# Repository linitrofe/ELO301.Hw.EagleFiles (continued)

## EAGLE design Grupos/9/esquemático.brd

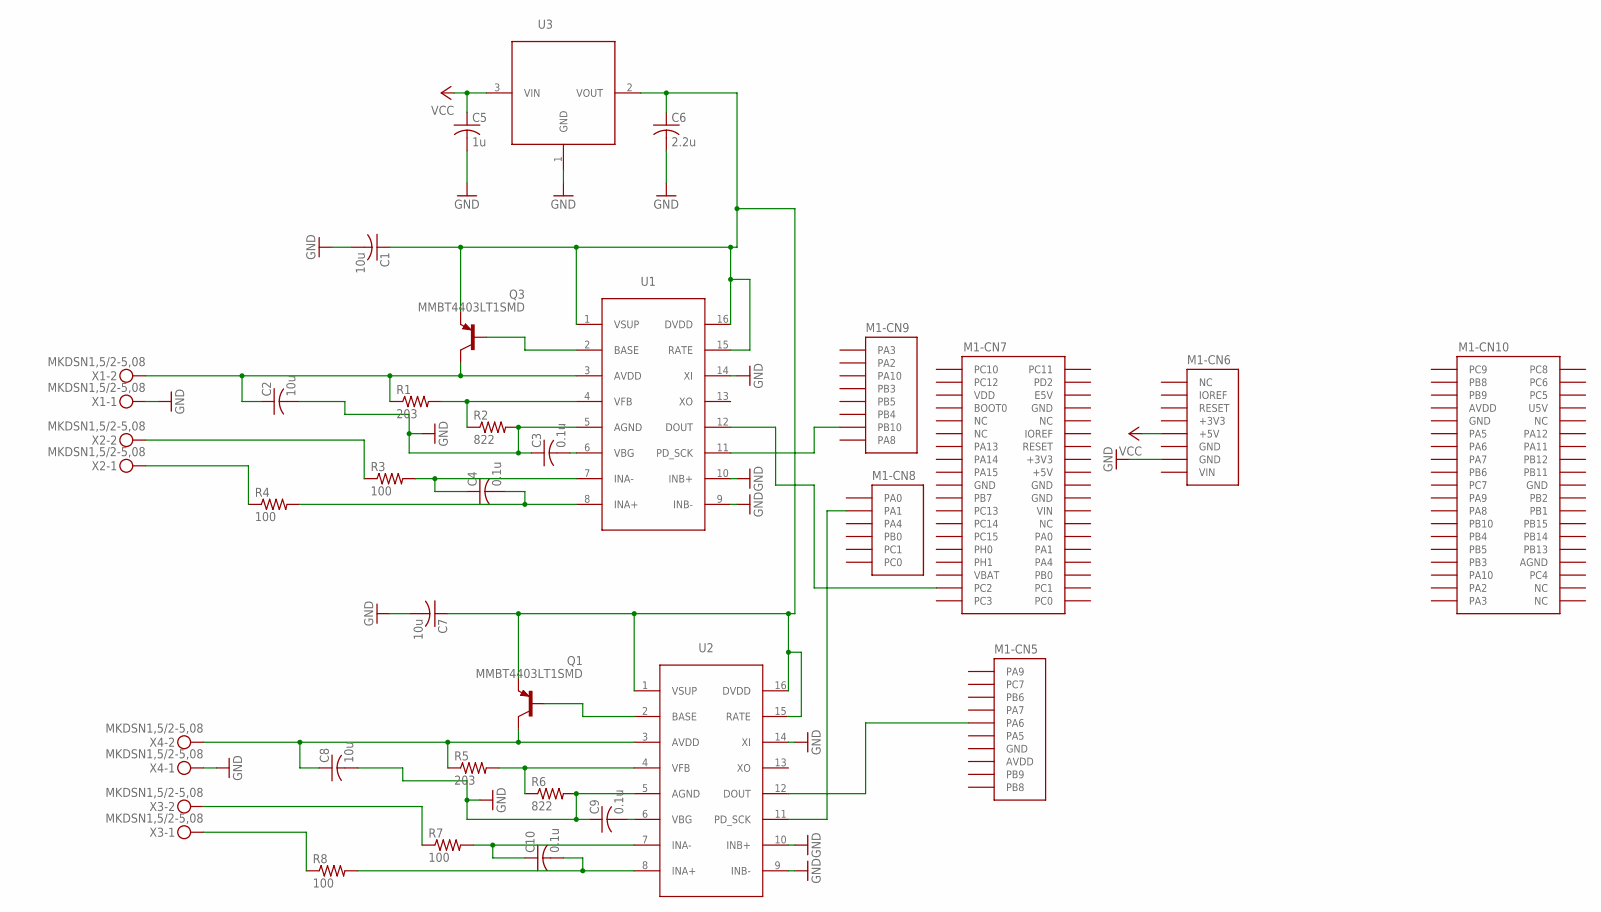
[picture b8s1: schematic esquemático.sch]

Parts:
C1, C2, C7, C8: 10u; C0805
C3, C4, C9, C10: 0.1u; C0805
C5: 1u; C0805
C6: 2.2u; C0805
M1: NUCLEO-L452RE; NUCLEO-64
Q1, Q3: MMBT4403LT1SMD; SOT23-BEC; PARTNO BCR573E6327
R1, R5: 203; R0805
R2, R6: 822; R0805
R3, R4, R7, R8: 100; R0805
U1, U2: HX711SOIC127P600X140-16N; SOIC127P600X140-16N; PARTNO HX711
U3: AP2210N-4.0TRG1; SOT-23-3; PARTNO AP2210N-4.0TRG1
X1, X2, X3, X4: MKDSN1,5/2-5,08; PARTNO MKDSN1,5/2-5,08

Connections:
+3V3: M1.CN6-4 (+3V3), M1.CN7-16 (+3V3)
+5V: M1.CN7-18 (+5V)
AGND: M1.CN10-32 (AGND)
AVDD: M1.CN5-8 (AVDD), M1.CN10-7 (AVDD)
GND: C1.2, C2.2, C3.1, C5.2, C6.2, C7.2, C8.2, C9.1, M1.CN5-7 (GND), M1.CN6-6 (GND), M1.CN6-7 (GND), M1.CN7-8 (GND), M1.CN7-19 (GND), M1.CN7-20 (GND), M1.CN7-22 (GND), M1.CN10-9 (GND), M1.CN10-20 (GND), R2.2, R6.2, U1.5 (AGND), U1.9 (INB-), U1.10 (INB+), U1.14 (XI), U2.5 (AGND), U2.9 (INB-), U2.10 (INB+), U2.14 (XI), U3.1 (GND), X1.1, X4.1
IOREF: M1.CN6-2 (IOREF)
unnamed: C2.1, Q3.C, R1.1, U1.3 (AVDD), X1.2
unnamed: C4.1, R3.2, U1.7 (INA-)
unnamed: M1.CN9-7 (PB10), U1.11 (PD_SCK)
unnamed: R1.2, R2.1, U1.4 (VFB)
unnamed: R3.1, X2.2
unnamed: C4.2, R4.2, U1.8 (INA+)
unnamed: R4.1, X2.1
unnamed: C3.2, U1.6 (VBG)
unnamed: C8.1, Q1.C, R5.1, U2.3 (AVDD), X4.2
unnamed: Q3.B, U1.2 (BASE)
unnamed: R5.2, R6.1, U2.4 (VFB)
unnamed: C10.1, R7.2, U2.7 (INA-)
unnamed: R7.1, X3.2
unnamed: C10.2, R8.2, U2.8 (INA+)
unnamed: R8.1, X3.1
unnamed: C9.2, U2.6 (VBG)
unnamed: M1.CN5-5 (PA6), U2.12 (DOUT)
unnamed: Q1.B, U2.2 (BASE)
unnamed: M1.CN7-35 (PC2), U1.12 (DOUT)
unnamed: M1.CN8-2 (PA1), U2.11 (PD_SCK)
unnamed: C1.1, C6.1, C7.1, Q1.E, Q3.E, U1.1 (VSUP), U1.15 (RATE), U1.16 (DVDD), U2.1 (VSUP), U2.15 (RATE), U2.16 (DVDD), U3.2 (VOUT)
U5V: M1.CN10-8 (U5V)
VBAT: M1.CN7-33 (VBAT)
VCC: C5.1, M1.CN6-5 (+5V), U3.3 (VIN)
VDD: M1.CN7-5 (VDD)
VIN: M1.CN6-8 (VIN), M1.CN7-24 (VIN)

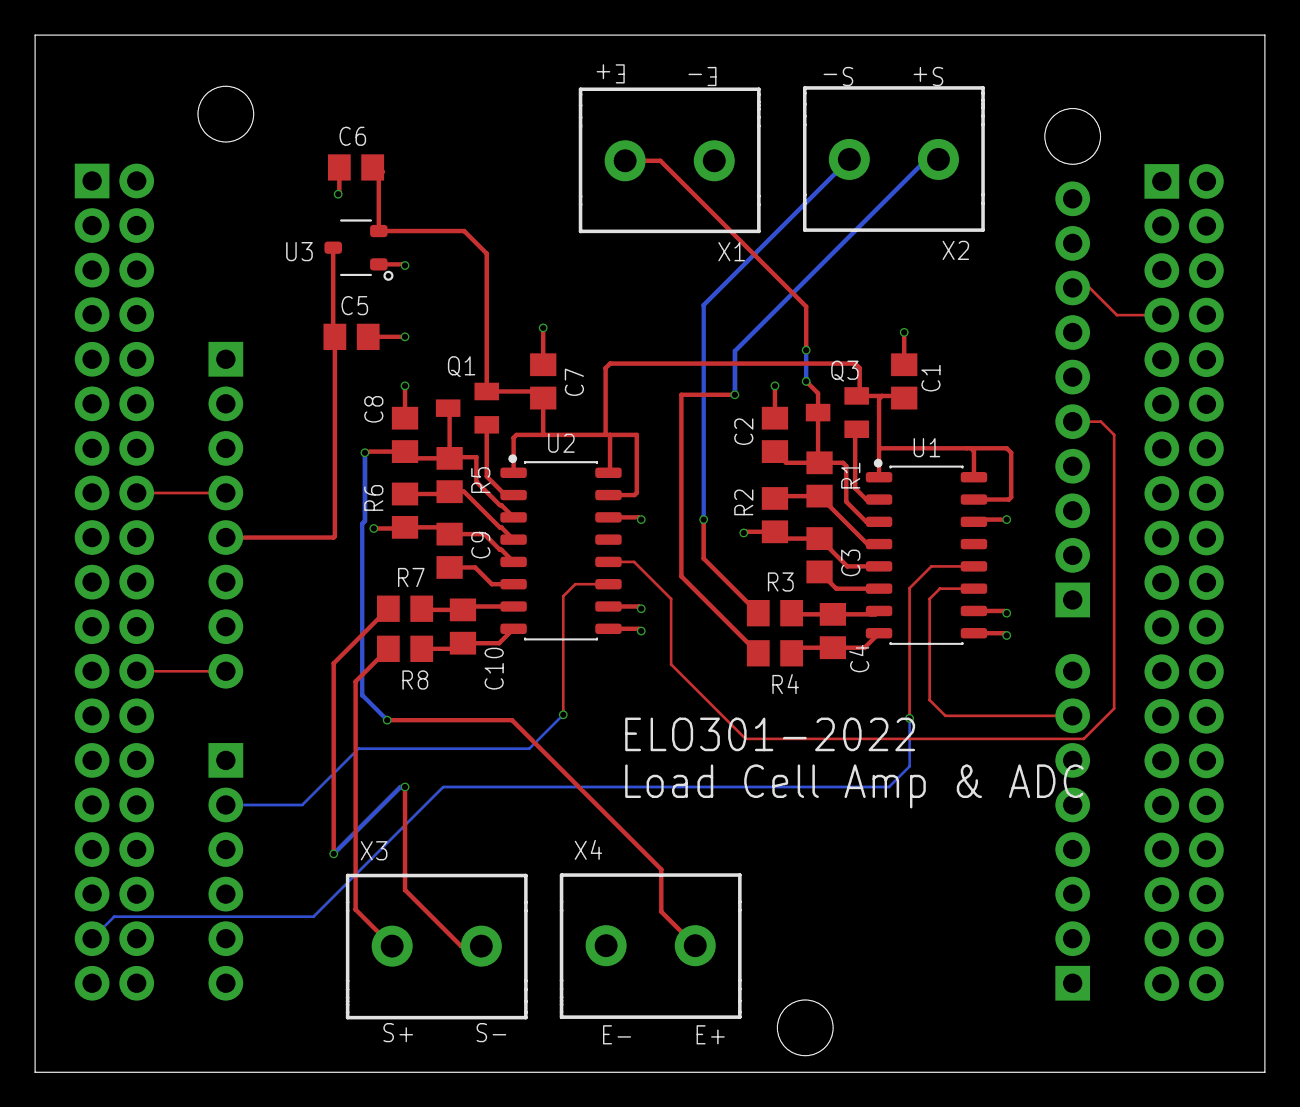
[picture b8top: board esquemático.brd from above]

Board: 2 copper layers, 70.1 x 59.1 mm, 28 parts (0 on the bottom side), 26 nets.

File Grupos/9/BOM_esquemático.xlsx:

Qty | Value | Device | Package | Parts | Description | PARTNO | POPULARITY | SPICEPREFIX | Column1
2 |  | HX711SOIC127P600X140-16N | SOIC127P600X140-16N | U1, U2 |  | HX711
1 |  | NUCLEO-L452RE | NUCLEO-64 | M1 | No existe un outline (Layer Dimension) para esta librería. En su lugar se utili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
4 | 0.1u | C-USC0805 | C0805 | C3, C4, C9, C10 | CAPACITOR, American symbol |  | 63 | C
4 | 100 | R-US_R0805 | R0805 | R3, R4, R7, R8 | RESISTOR, American symbol |  | 85 | R
4 | 10u | C-USC0805 | C0805 | C1, C2, C7, C8 | CAPACITOR, American symbol |  | 63 | C
1 | 1u | C-USC0805 | C0805 | C5 | CAPACITOR, American symbol |  | 63 | C
1 | 2.2u | C-USC0805 | C0805 | C6 | CAPACITOR, American symbol |  | 63 | C
2 | 203 | R-US_R0805 | R0805 | R1, R5 | RESISTOR, American symbol |  | 85 | R
2 | 822 | R-US_R0805 | R0805 | R2, R6 | RESISTOR, American symbol |  | 85 | R
1 | AP2210N-4.0TRG1 | AP2210N-4.0TRG1 | SOT-23-3 | U3 |  | AP2210N-4.0TRG1
4 | MKDSN1,5/2-5,08 | MKDSN1,5/2-5,08 | MKDSN1,5/2-5,08 | X1, X2, X3, X4 | MKDSN 1,5/ 2-5,08 Printklemme | MKDSN1,5/2-5,08 | 14
2 | MMBT4403LT1SMD | MMBT4403LT1SMD | SOT23-BEC | Q1, Q3 | PNP Transistror | BCR573E6327 | 1

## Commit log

2022-11-09 Se agrega la librería para la NUCLEO-L452RE
2022-11-09 Se actualiza el nombre de la carpeta
2022-11-17 Se suben todas las entregas
2022-11-17 Se suben archivos de fabricación del grupo 3
2022-11-18 Revisión en progreso
2022-11-19 Se agregan archivos de proyecto del grupo8
2022-11-19 Se arregla error crítico en la fuente de poder
2022-11-19 Se agregan resistencias de CC, sin embargo una debe ser cableada manualmente
2022-11-19 FAltó guardar
2022-11-19 Se agrea el zer-cross, se cambian señales de luar, se arregla el botón
2022-11-19 Se mueve el RS485 a UART4
2022-11-19 Se cablean los ADC a SPI1 y SPI2
2022-11-19 Swap RTS/CTS and RX/TX
2022-11-22 Se arregla JST
2022-11-22 Se arregla botón
2022-11-22 Se arregla diametro agujero pote
2022-11-22 Se arregla librerías
2022-11-23 Nuevo proyecto grupo
2022-11-23 Se finaliza tarjeta grupo 2
2022-11-23 Archivos que se envian a fabricación
2022-12-16 Se suben archivos posterior a revisión
